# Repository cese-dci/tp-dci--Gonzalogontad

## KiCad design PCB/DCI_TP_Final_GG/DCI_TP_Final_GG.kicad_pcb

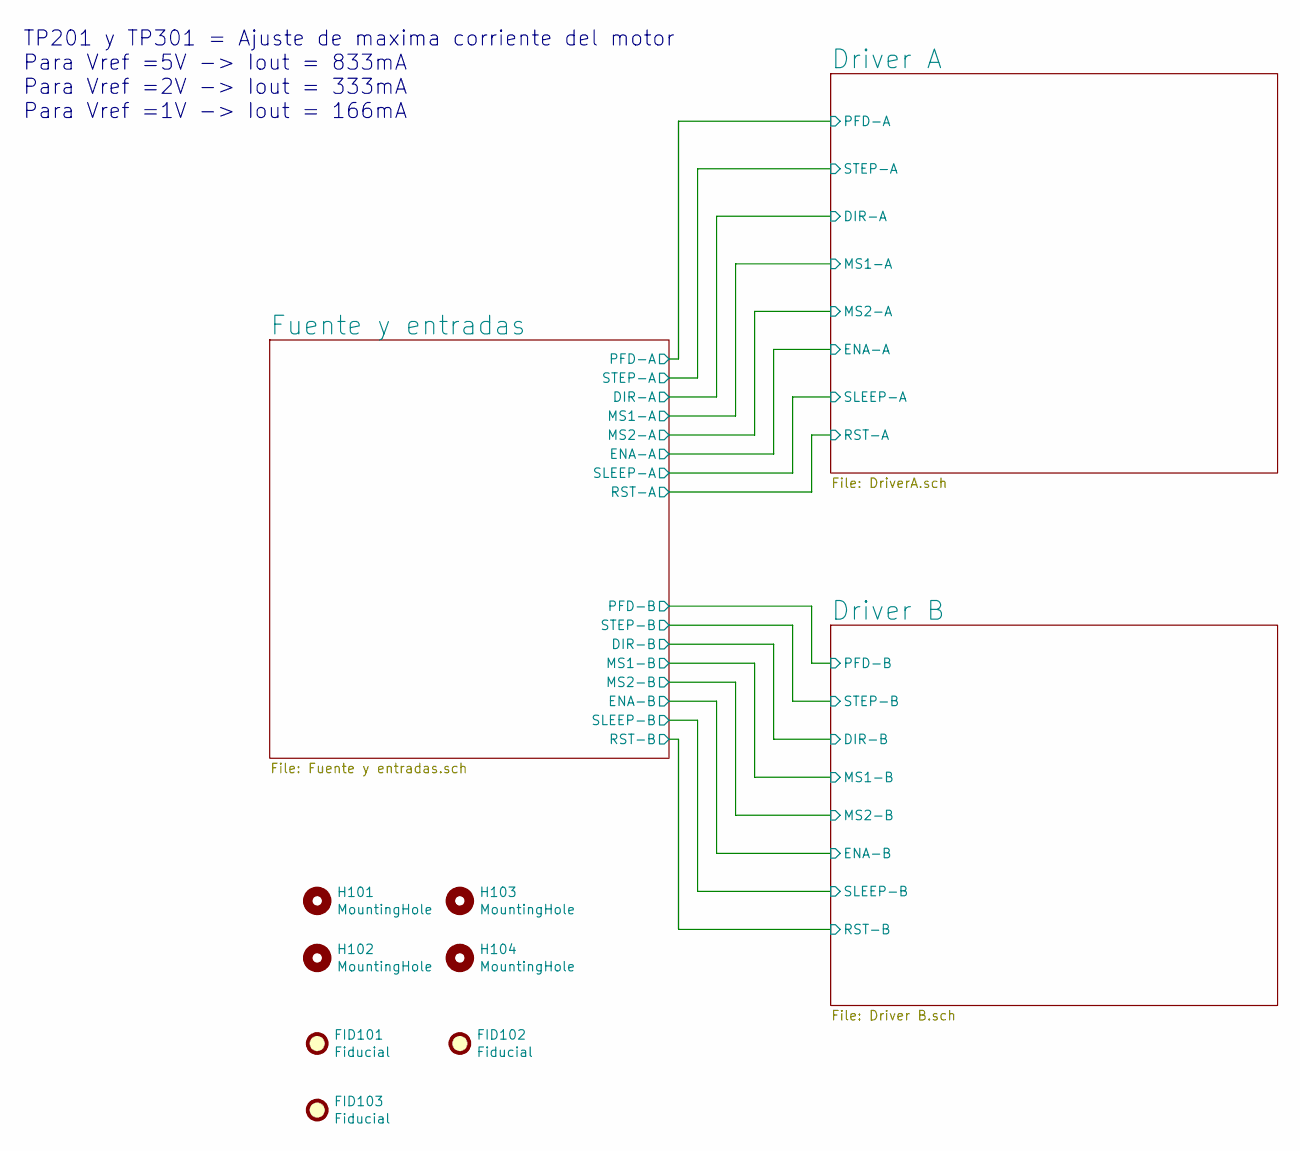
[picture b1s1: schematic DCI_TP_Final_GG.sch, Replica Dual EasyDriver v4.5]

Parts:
FID101, FID102, FID103: Fiducial; Fiducial_1mm_Mask2mm
H101, H102, H103, H104: MountingHole; MountingHole_3mm

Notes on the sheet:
TP201 y TP301 = Ajuste de maxima corriente del motor Para Vref =5V -> Iout = 833mA Para Vref =2V -> Iout = 333mA Para Vref =1V -> Iout = 166mA

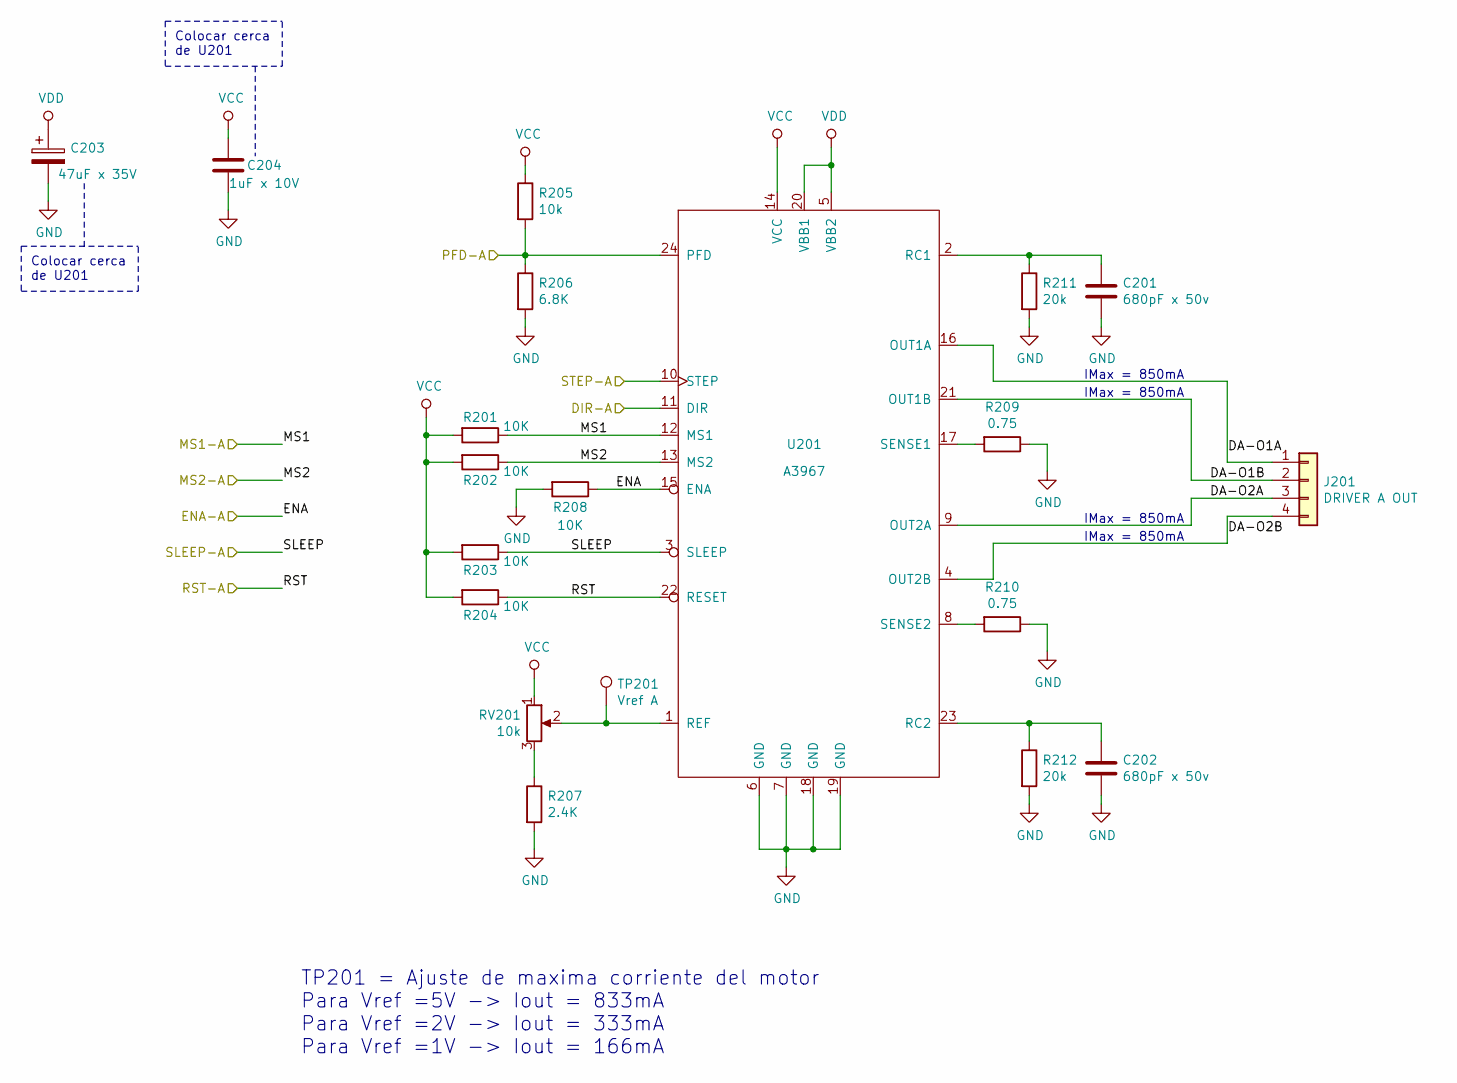
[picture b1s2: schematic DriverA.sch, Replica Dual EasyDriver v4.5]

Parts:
C201, C202: 680pF x 50v; C_0805_2012Metric; digikey# 399-8110-1-ND
C203: 47uF x 35V; CP_Radial_D5.0mm_P2.00mm; digikey# 493-11044-1-ND
C204: 1uF x 10V; C_0805_2012Metric; digikey# 399-1172-1-ND
J201: DRIVER A OUT; TerminalBlock_Phoenix_MKDS-1,5-4_1x04_P5.00mm_Horizontal; digikey# 277-1238-ND
R201, R202, R203, R204, R208: 10K; R_0805_2012Metric; digikey# 311-10KARCT-ND
R205: 10k; R_0805_2012Metric; digikey# 311-10KARCT-ND
R206: 6.8K; R_0805_2012Metric; digikey# 311-6.80KCRCT-ND
R207: 2.4K; R_0805_2012Metric; digikey# 311-2.40KCRCT-ND
R209, R210: 0.75; R_0805_2012Metric; digikey# RCWE.75DCT-ND
R211, R212: 20k; R_0805_2012Metric; digikey# 311-20.0KCRCT-ND
RV201: 10k; Potentiometer_Vishay_TS53YJ_Vertical; digikey# TS53YJ-10KTR-ND
TP201: Vref A; TestPoint_Pad_D2.0mm
U201: A3967; SOIC-24W_7.5x15.4mm_P1.27mm; digikey# 620-1140-1-ND

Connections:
/Driver A/DA-O1A: J201.1, U201.16 (OUT1A)
/Driver A/DA-O1B: J201.2, U201.21 (OUT1B)
/Driver A/DA-O2A: J201.3, U201.9 (OUT2A)
/Driver A/DA-O2B: J201.4, U201.4 (OUT2B)
/Driver A/DIR-A: U201.11 (DIR); also elsewhere on the board
/Driver A/ENA-A: R208.1, U201.15 (ENA); also elsewhere on the board
/Driver A/MS1-A: R201.1, U201.12 (MS1); also elsewhere on the board
/Driver A/MS2-A: R202.1, U201.13 (MS2); also elsewhere on the board
/Driver A/PFD-A: R205.2, R206.1, U201.24 (PFD); also elsewhere on the board
/Driver A/RST-A: R204.1, U201.22 (RESET); also elsewhere on the board
/Driver A/SLEEP-A: R203.1, U201.3 (SLEEP); also elsewhere on the board
/Driver A/STEP-A: U201.10 (STEP); also elsewhere on the board
GND: C201.2, C202.2, C203.2, C204.2, R206.2, R207.2, R208.2, R209.1, R210.1, R211.2, R212.2, U201.6 (GND), U201.7 (GND), U201.18 (GND), U201.19 (GND); also elsewhere on the board
unnamed: C201.1, R211.1, U201.2 (RC1)
unnamed: C202.1, R212.1, U201.23 (RC2)
unnamed: R207.1, RV201.3
unnamed: R209.2, U201.17 (SENSE1)
unnamed: R210.2, U201.8 (SENSE2)
unnamed: RV201.2, TP201.1, U201.1 (REF)
VCC: C204.1, R201.2, R202.2, R203.2, R204.2, R205.1, RV201.1, U201.14 (VCC); also elsewhere on the board
VDD: C203.1, U201.5 (VBB2), U201.20 (VBB1); also elsewhere on the board

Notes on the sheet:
IMax = 850mA
TP201 = Ajuste de maxima corriente del motor Para Vref =5V -> Iout = 833mA Para Vref =2V -> Iout = 333mA Para Vref =1V -> Iout = 166mA
Colocar cerca de U201

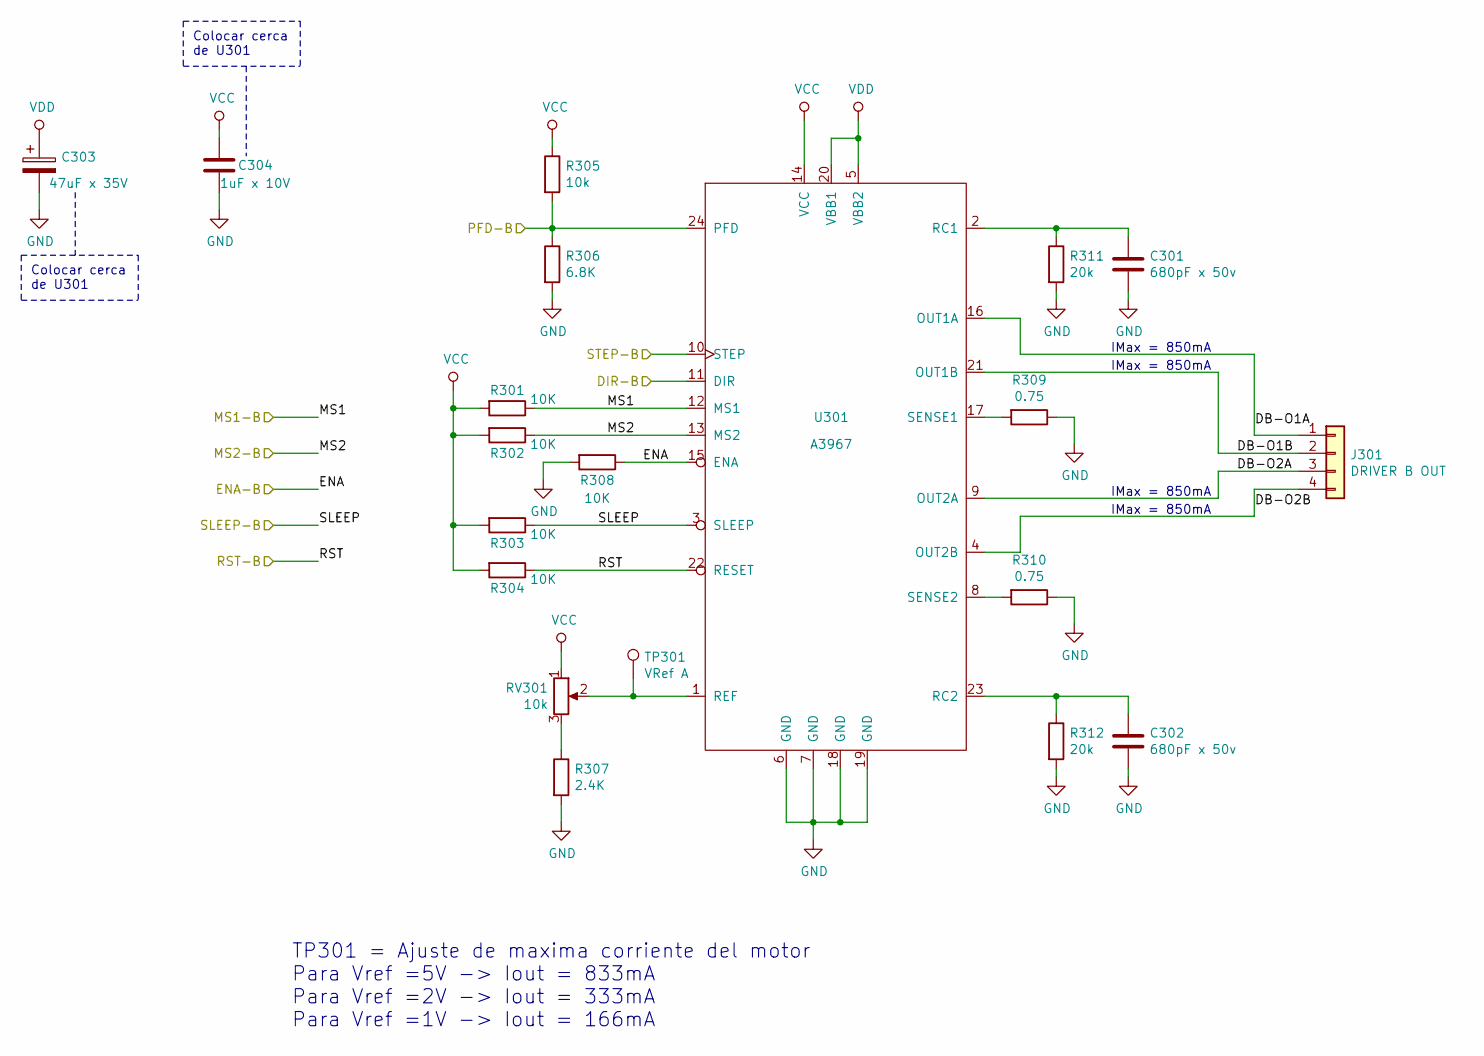
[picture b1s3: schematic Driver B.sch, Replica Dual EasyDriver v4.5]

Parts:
C301, C302: 680pF x 50v; C_0805_2012Metric; digikey# 399-8110-1-ND
C303: 47uF x 35V; CP_Radial_D5.0mm_P2.00mm; digikey# 493-11044-1-ND
C304: 1uF x 10V; C_0805_2012Metric; digikey# 399-1172-1-ND
J301: DRIVER B OUT; TerminalBlock_Phoenix_MKDS-1,5-4_1x04_P5.00mm_Horizontal; digikey# 277-1238-ND
R301, R302, R303, R304, R308: 10K; R_0805_2012Metric; digikey# 311-10KARCT-ND
R305: 10k; R_0805_2012Metric; digikey# 311-10KARCT-ND
R306: 6.8K; R_0805_2012Metric; digikey# 311-6.80KCRCT-ND
R307: 2.4K; R_0805_2012Metric; digikey# 311-2.40KCRCT-ND
R309, R310: 0.75; R_0805_2012Metric; digikey# RCWE.75DCT-ND
R311, R312: 20k; R_0805_2012Metric; digikey# 311-20.0KCRCT-ND
RV301: 10k; Potentiometer_Vishay_TS53YJ_Vertical; digikey# TS53YJ-10KTR-ND
TP301: VRef A; TestPoint_Pad_D2.0mm
U301: A3967; SOIC-24W_7.5x15.4mm_P1.27mm; digikey# 620-1140-1-ND

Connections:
/Driver B/DB-O1A: J301.1, U301.16 (OUT1A)
/Driver B/DB-O1B: J301.2, U301.21 (OUT1B)
/Driver B/DB-O2A: J301.3, U301.9 (OUT2A)
/Driver B/DB-O2B: J301.4, U301.4 (OUT2B)
/Driver B/DIR-B: U301.11 (DIR); also elsewhere on the board
/Driver B/ENA-B: R308.1, U301.15 (ENA); also elsewhere on the board
/Driver B/MS1-B: R301.1, U301.12 (MS1); also elsewhere on the board
/Driver B/MS2-B: R302.1, U301.13 (MS2); also elsewhere on the board
/Driver B/PFD-B: R305.2, R306.1, U301.24 (PFD); also elsewhere on the board
/Driver B/RST-B: R304.1, U301.22 (RESET); also elsewhere on the board
/Driver B/SLEEP-B: R303.1, U301.3 (SLEEP); also elsewhere on the board
/Driver B/STEP-B: U301.10 (STEP); also elsewhere on the board
GND: C301.2, C302.2, C303.2, C304.2, R306.2, R307.2, R308.2, R309.1, R310.1, R311.2, R312.2, U301.6 (GND), U301.7 (GND), U301.18 (GND), U301.19 (GND); also elsewhere on the board
unnamed: C301.1, R311.1, U301.2 (RC1)
unnamed: C302.1, R312.1, U301.23 (RC2)
unnamed: R307.1, RV301.3
unnamed: R309.2, U301.17 (SENSE1)
unnamed: R310.2, U301.8 (SENSE2)
unnamed: RV301.2, TP301.1, U301.1 (REF)
VCC: C304.1, R301.2, R302.2, R303.2, R304.2, R305.1, RV301.1, U301.14 (VCC); also elsewhere on the board
VDD: C303.1, U301.5 (VBB2), U301.20 (VBB1); also elsewhere on the board

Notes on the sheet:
IMax = 850mA
TP301 = Ajuste de maxima corriente del motor Para Vref =5V -> Iout = 833mA Para Vref =2V -> Iout = 333mA Para Vref =1V -> Iout = 166mA
Colocar cerca de U301

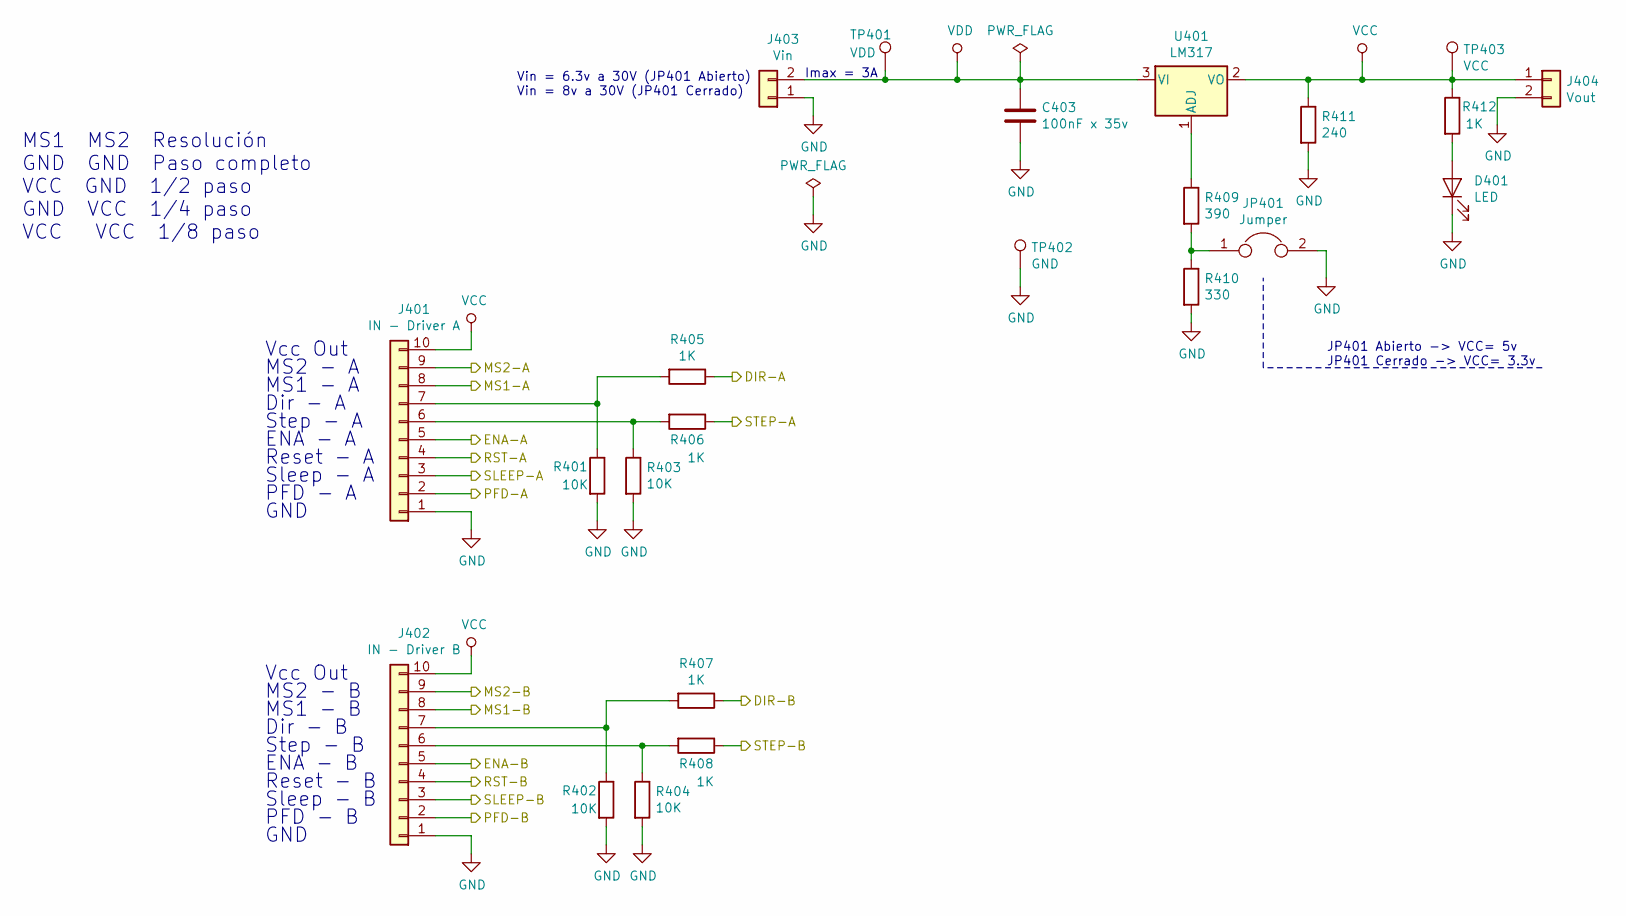
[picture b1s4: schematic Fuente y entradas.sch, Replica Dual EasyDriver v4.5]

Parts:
C403: 100nF x 35v; C_0805_2012Metric; digikey# 587-3364-1-ND
D401: LED; LED_D3.0mm; digikey# 1516-1350-ND
J401: IN - Driver A; PinHeader_1x10_P2.54mm_Vertical; digikey# WM20125-ND
J402: IN - Driver B; PinHeader_1x10_P2.54mm_Vertical; digikey# WM20125-ND
J403: Vin; TerminalBlock_Phoenix_MKDS-1,5-2_1x02_P5.00mm_Horizontal; digikey# 277-1258-ND
J404: Vout; PinHeader_1x02_P2.54mm_Vertical; digikey# 952-2262-ND
JP401: Jumper; R_0805_2012Metric; digikey# CR0805-J/-000ELFCT-ND
R401, R402, R403, R404: 10K; R_0805_2012Metric; digikey# 311-10KARCT-ND
R405, R406, R407, R408, R412: 1K; R_0805_2012Metric; digikey# 311-1.00CRCT-ND
R409: 390; R_0805_2012Metric; digikey# 311-390CRCT-ND
R410: 330; R_0805_2012Metric; digikey# 311-330CRCT-ND
R411: 240; R_0805_2012Metric; digikey# 311-.24SCT-ND
TP401: VDD; TestPoint_Pad_D2.0mm
TP402: GND; TestPoint_Pad_D2.0mm
TP403: VCC; TestPoint_Pad_D2.0mm
U401: LM317; SOT-223-3_TabPin2; digikey# LM317MSTT3GOSCT-ND

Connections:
/Driver A/DIR-A: R405.1; also elsewhere on the board
/Driver A/ENA-A: J401.5; also elsewhere on the board
/Driver A/MS1-A: J401.8; also elsewhere on the board
/Driver A/MS2-A: J401.9; also elsewhere on the board
/Driver A/PFD-A: J401.2; also elsewhere on the board
/Driver A/RST-A: J401.4; also elsewhere on the board
/Driver A/SLEEP-A: J401.3; also elsewhere on the board
/Driver A/STEP-A: R406.1; also elsewhere on the board
/Driver B/DIR-B: R407.1; also elsewhere on the board
/Driver B/ENA-B: J402.5; also elsewhere on the board
/Driver B/MS1-B: J402.8; also elsewhere on the board
/Driver B/MS2-B: J402.9; also elsewhere on the board
/Driver B/PFD-B: J402.2; also elsewhere on the board
/Driver B/RST-B: J402.4; also elsewhere on the board
/Driver B/SLEEP-B: J402.3; also elsewhere on the board
/Driver B/STEP-B: R408.1; also elsewhere on the board
GND: C403.2, D401.1 (K), J401.1, J402.1, J403.1, J404.2, JP401.2, R401.2, R402.2, R403.2, R404.2, R410.2, R411.2, TP402.1; also elsewhere on the board
unnamed: D401.2 (A), R412.2
unnamed: J401.6, R403.1, R406.2
unnamed: J401.7, R401.1, R405.2
unnamed: J402.6, R404.1, R408.2
unnamed: J402.7, R402.1, R407.2
unnamed: JP401.1, R409.2, R410.1
unnamed: R409.1, U401.1 (ADJ)
VCC: J401.10, J402.10, J404.1, R411.1, R412.1, TP403.1, U401.2 (VO); also elsewhere on the board
VDD: C403.1, J403.2, TP401.1, U401.3 (VI); also elsewhere on the board

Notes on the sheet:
Vin = 6.3v a 30V (JP401 Abierto) Vin = 8v a 30V (JP401 Cerrado)
JP401 Abierto -> VCC= 5v JP401 Cerrado -> VCC= 3.3v
Vcc Out
Step - A
Dir - A
MS1 - A
MS2 - A
ENA - A
Reset - A
Sleep - A
PFD - A
GND
Step - B
Dir - B
MS1 - B
MS2 - B
ENA - B
Reset - B
Sleep - B
PFD - B
MS1 MS2 Resolución GND GND Paso completo VCC GND 1/2 paso GND VCC 1/4 paso VCC VCC 1/8 paso
Imax = 3A

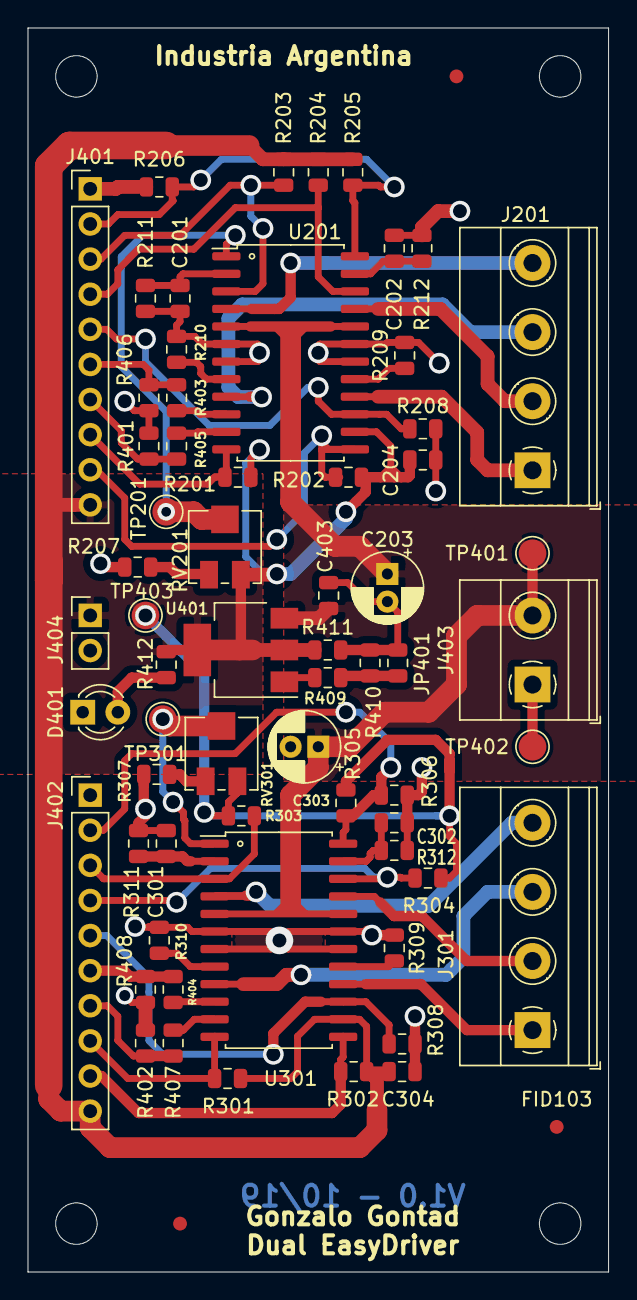
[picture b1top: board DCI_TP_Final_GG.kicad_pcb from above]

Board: 2 copper layers, 42.0 x 90.0 mm, 70 parts (0 on the bottom side), 46 nets.

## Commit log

2019-09-17 Agrego archivos de la propuesta de TP para DCI
2019-09-17 Cambio de nombre a carpeta Documentacion Previa por info
2019-10-02 Creo carpeta PCB y creo el proyecto del PCB en Kicad
2019-10-04 3/10/2019 Creacion de la jerarquia de archivos para el esquematico Dibujo Driver A y Driver B
2019-10-04 Agrego esquematico de fuente (falta completar)
2019-10-04 Hoja de fuente y conectores completa.
2019-10-05 Se completo el esquematico y documentación. El esquematico esta listo para una primera revisión.
2019-10-05 Update README.md
    corrección ortografica
2019-10-08 Agrego datasheet faltante, foto y biblioteca de componente.
2019-10-10 Inicio etapa de desarrollo de PCB, agrego biblioteca de borneras
2019-10-10 Avance en el routeo
2019-10-11 avance en pcb
2019-10-11 Avance en routeo
2019-10-14 avance en ruteo de PCB
2019-10-14 Avance en routeo de PCB
2019-10-17 Agrego 3D de borneras
2019-10-18 Agrego codigos de catalogo
2019-10-18 Version para revision de PCB Exporto modelos 3d y archivos de fabricacion
2019-10-26 Cambio de ubicacion de capacitores de desacople en la jerarquia del esquematico y actualizacion de identificadores en PCB
2019-11-15 Correccion de Plano de masa
2019-11-19 Cambio Versión en PCB
